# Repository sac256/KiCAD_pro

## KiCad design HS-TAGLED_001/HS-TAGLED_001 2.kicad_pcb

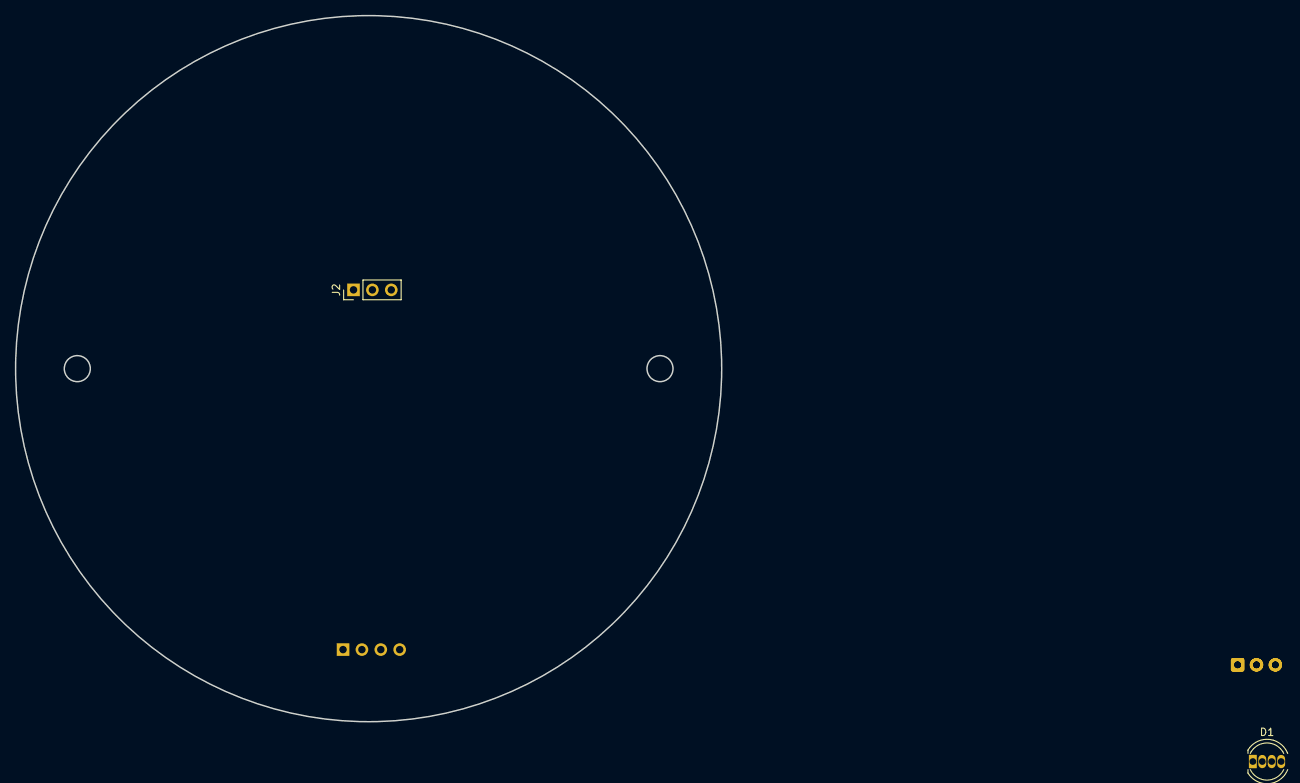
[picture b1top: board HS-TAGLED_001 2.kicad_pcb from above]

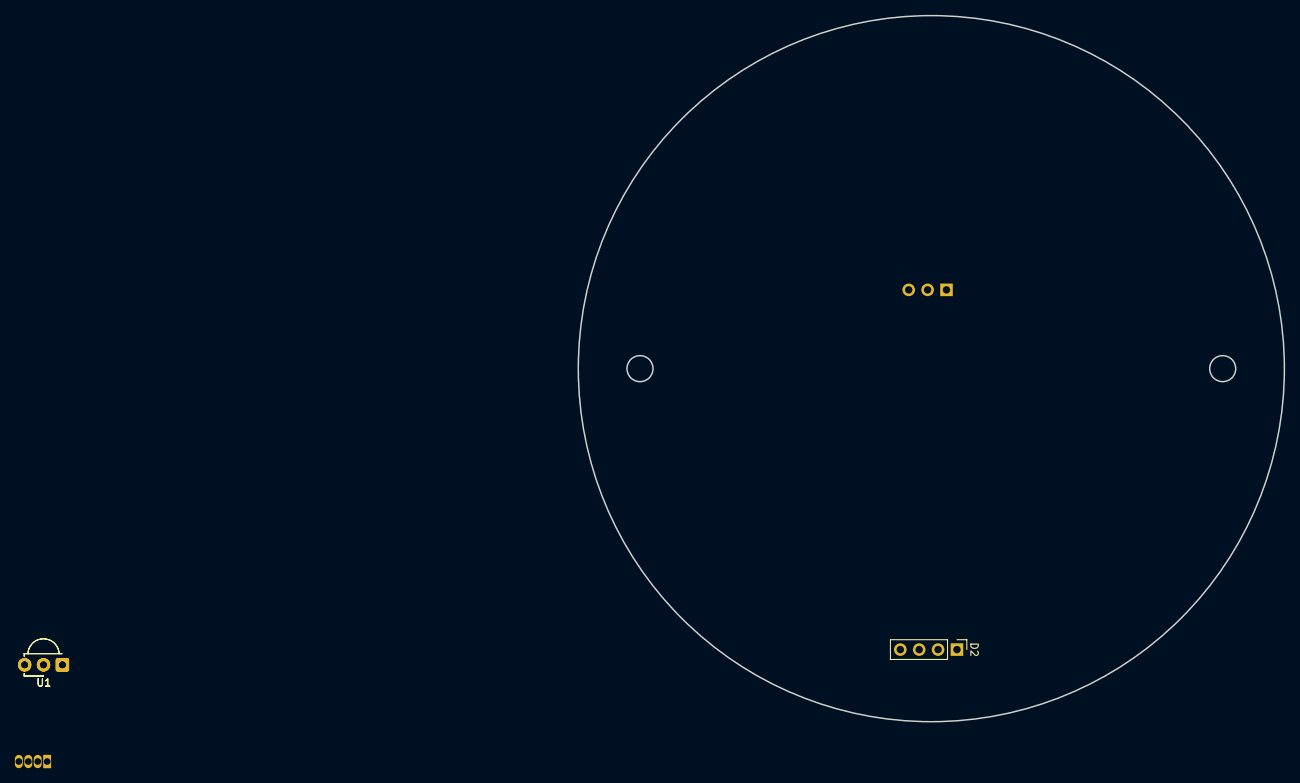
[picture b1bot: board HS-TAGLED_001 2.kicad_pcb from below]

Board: 2 copper layers, 95.0 x 95.0 mm, 5 parts (3 on the bottom side), 7 nets, no tracks yet.

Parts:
D1: LED_ARGB; LED_D5.0mm-4_RGB
D2: LED_ARGB; PinHeader_1x04_P2.54mm_Vertical
J2: Conn_01x03; PinHeader_1x03_P2.54mm_Vertical
U1, U1#2: TSOP59540TR1; Vishay_MINICAST-3Pin

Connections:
unnamed: D1.1, D2.1
unnamed: D1.2, D2.2
unnamed: D1.3, D2.3
unnamed: D1.4, D2.4
unnamed: J2.1, U1.1, U1#2.1
unnamed: J2.2, U1.2, U1#2.2
unnamed: J2.3, U1.3, U1#2.3

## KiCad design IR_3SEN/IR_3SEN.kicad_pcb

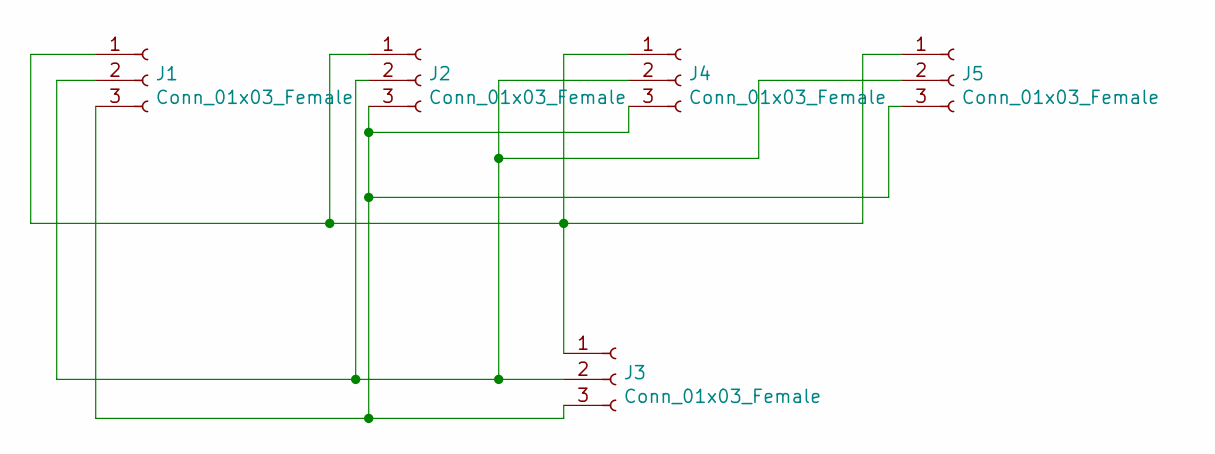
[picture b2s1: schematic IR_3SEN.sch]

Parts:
J1, J2, J3, J4, J5: Conn_01x03_Female; FanPinHeader_1x03_P2.54mm_Vertical

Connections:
unnamed: J1.1, J2.1, J3.1, J4.1, J5.1
unnamed: J1.2, J2.2, J3.2, J4.2, J5.2
unnamed: J1.3, J2.3, J3.3, J4.3, J5.3

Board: 2 copper layers, 5 parts (0 on the bottom side), 3 nets, no tracks yet.
